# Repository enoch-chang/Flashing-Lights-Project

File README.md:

# Flashing-Lights-Project

Lights will be flashing.

Demo: https://youtu.be/DI44GL3oFzs

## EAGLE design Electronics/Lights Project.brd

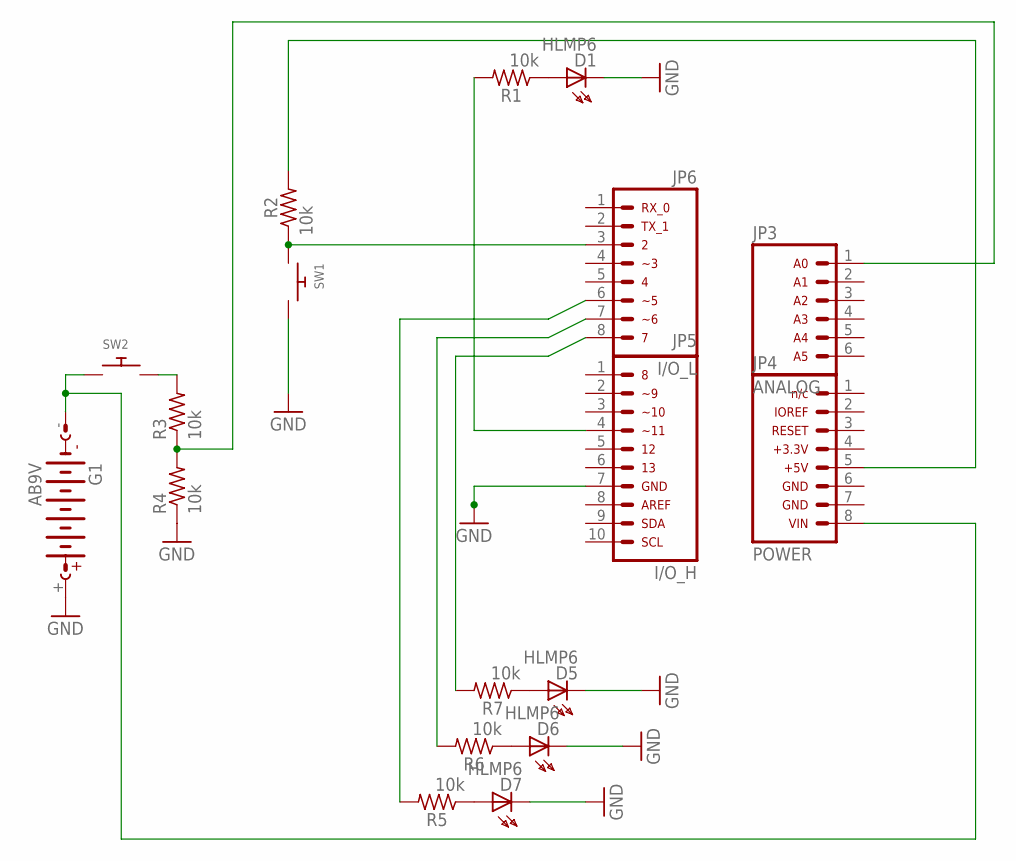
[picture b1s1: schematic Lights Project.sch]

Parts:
D1, D5, D6, D7: HLMP6
G1: AB9V
JP3: ARDUINO_CONN-ANALOGSIP; CONN-1X06
JP4: ARDUINO_CONN-POWERSIP; CONN-1X08
JP5: ARDUINO_CONN-IO_HSIP; CONN-1X10
JP6: ARDUINO_CONN-IO_LSIP; CONN-1X08
R1, R2, R3, R4, R5, R6, R7: 10k; R0805
SW1, SW2: SWITCH_PUSHBUTTONSOFTTOUCHSMD_SJ; PUSHBUTTON_SMD_SJ

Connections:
GND: D1.K, D5.K, D6.K, D7.K, G1.+, JP5.7, R4.1, SW1.P$2
unnamed: G1.-, JP4.8, SW2.P$1
unnamed: JP5.4, R1.2
unnamed: D1.A, R1.1
unnamed: D5.A, R7.1
unnamed: JP6.3, R2.1, SW1.P$1
unnamed: R3.2, SW2.P$2
unnamed: D6.A, R6.1
unnamed: JP6.6, R5.2
unnamed: D7.A, R5.1
unnamed: JP6.7, R6.2
unnamed: JP6.8, R7.2
unnamed: JP3.1, R3.1, R4.2
unnamed: JP4.5, R2.2

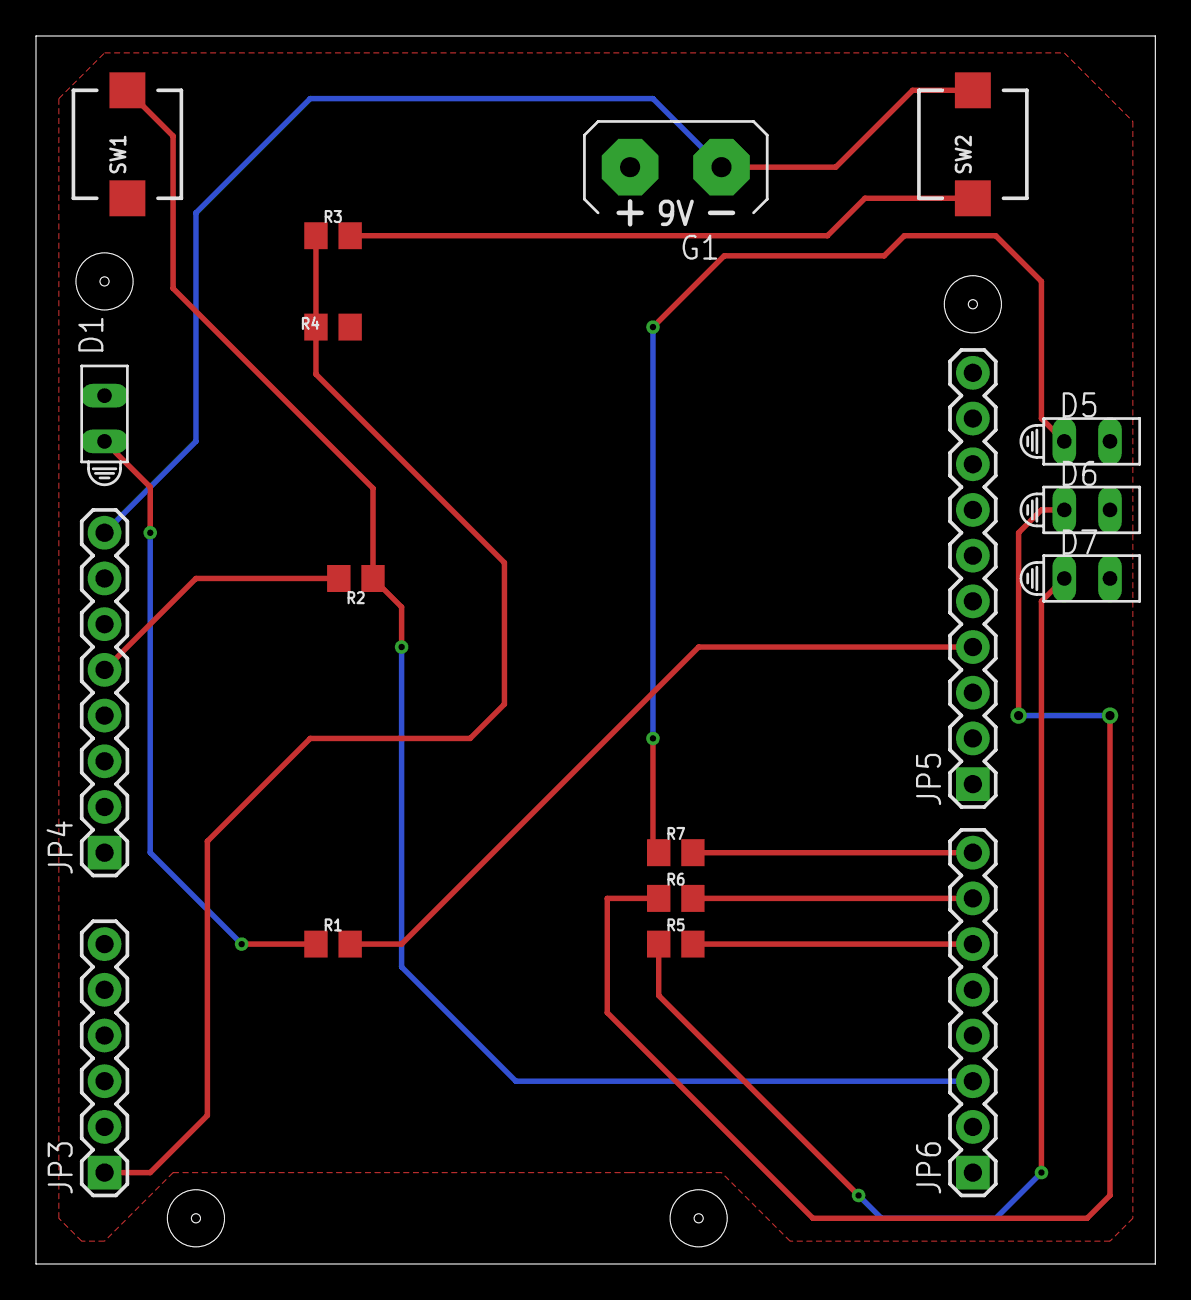
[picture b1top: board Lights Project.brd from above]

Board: 2 copper layers, 62.2 x 68.2 mm, 18 parts (0 on the bottom side), 14 nets.

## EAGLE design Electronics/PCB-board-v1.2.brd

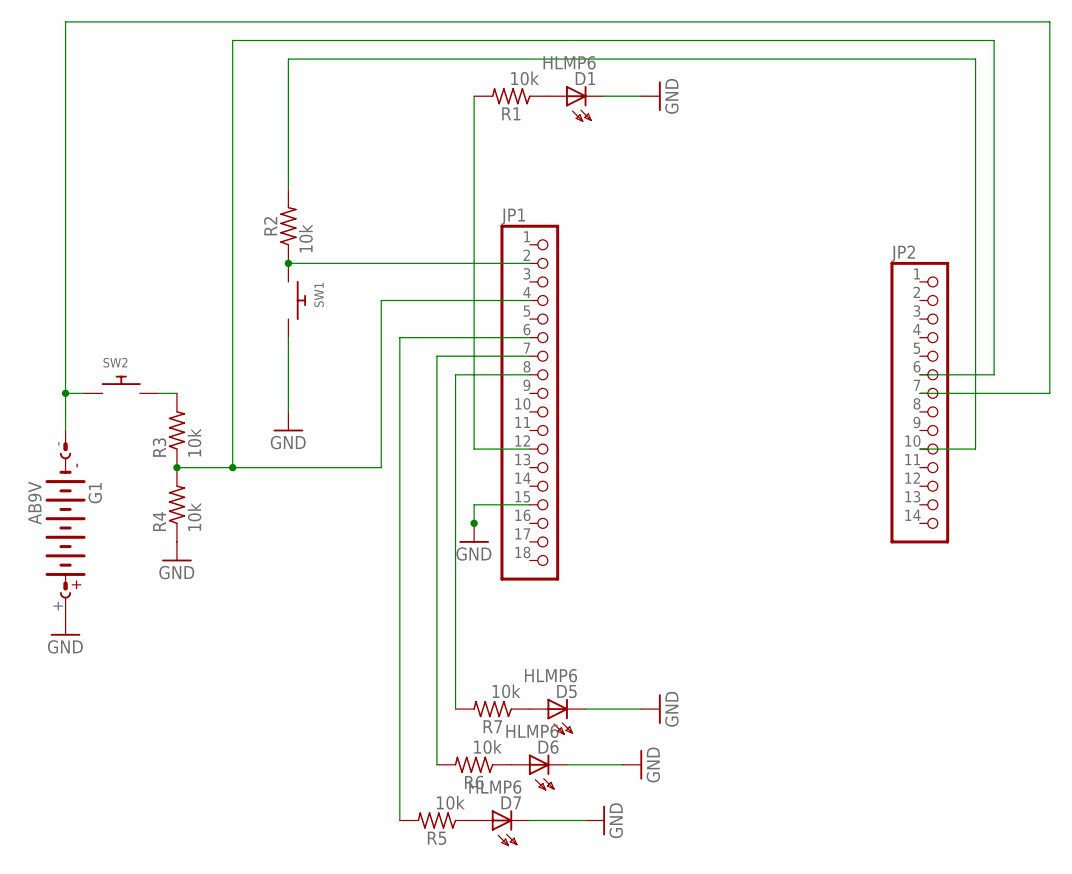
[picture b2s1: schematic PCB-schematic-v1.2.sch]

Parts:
D1, D5, D6, D7: HLMP6
G1: AB9V
JP1: PINHD-1X18; 1X18
JP2: PINHD-1X14; 1X14
R1, R2, R3, R4, R5, R6, R7: 10k; R0805
SW1, SW2: SWITCH_PUSHBUTTONSOFTTOUCHSMD_SJ; PUSHBUTTON_SMD_SJ

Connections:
GND: D1.K, D5.K, D6.K, D7.K, G1.+, JP1.15, R4.1, SW1.P$2
unnamed: G1.-, JP2.7, SW2.P$1
unnamed: JP1.12, R1.2
unnamed: D1.A, R1.1
unnamed: D5.A, R7.1
unnamed: JP1.2, R2.1, SW1.P$1
unnamed: R3.2, SW2.P$2
unnamed: D6.A, R6.1
unnamed: JP1.6, R5.2
unnamed: D7.A, R5.1
unnamed: JP1.7, R6.2
unnamed: JP1.8, R7.2
unnamed: JP1.4, JP2.6, R3.1, R4.2
unnamed: JP2.10, R2.2

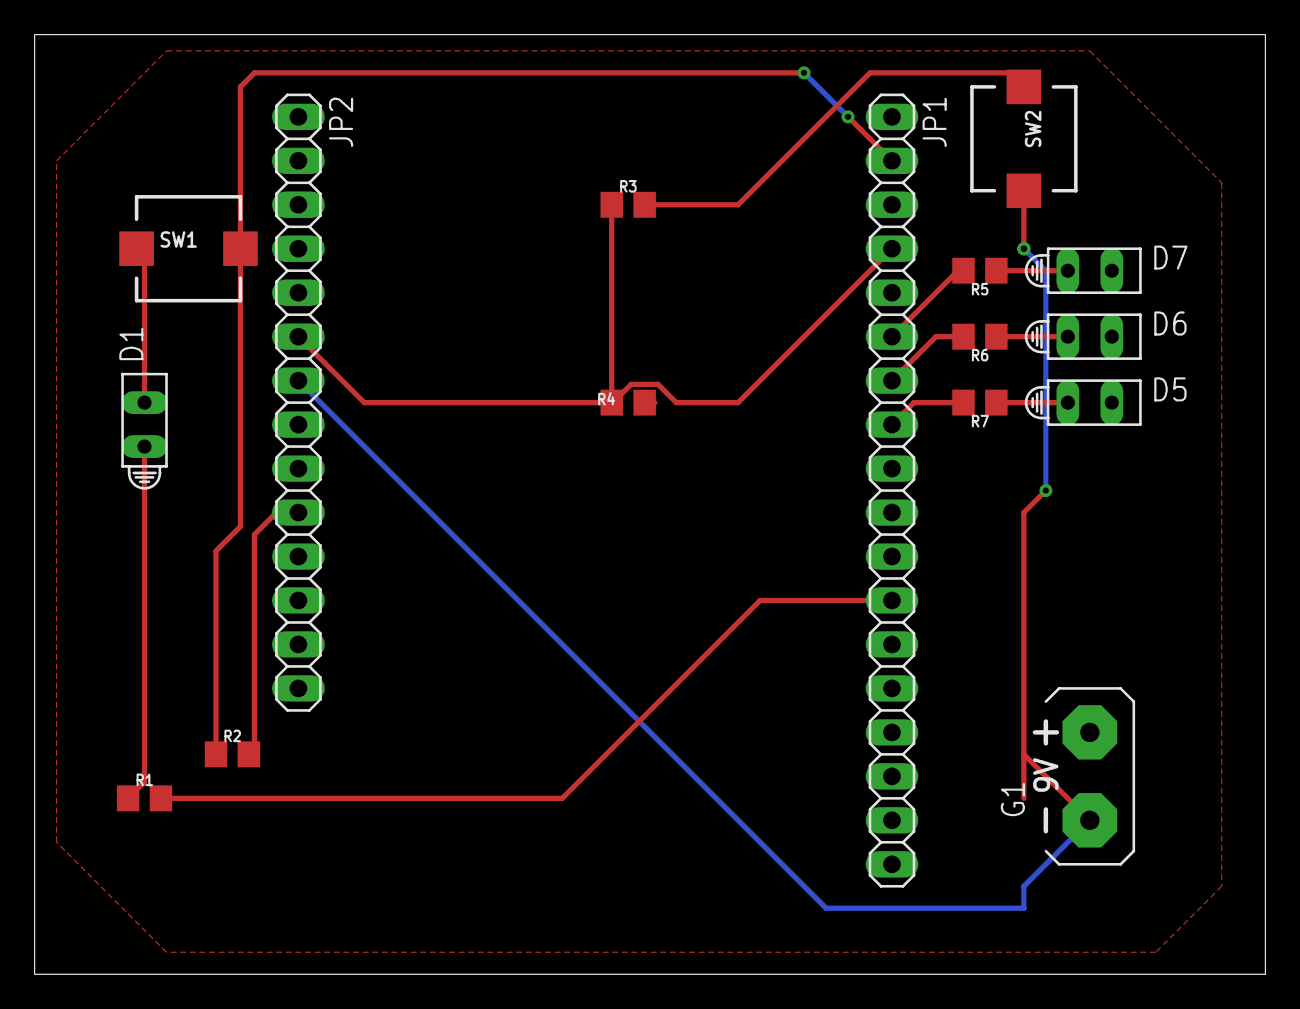
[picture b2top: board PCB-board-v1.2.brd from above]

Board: 2 copper layers, 71.1 x 54.3 mm, 16 parts (0 on the bottom side), 14 nets.

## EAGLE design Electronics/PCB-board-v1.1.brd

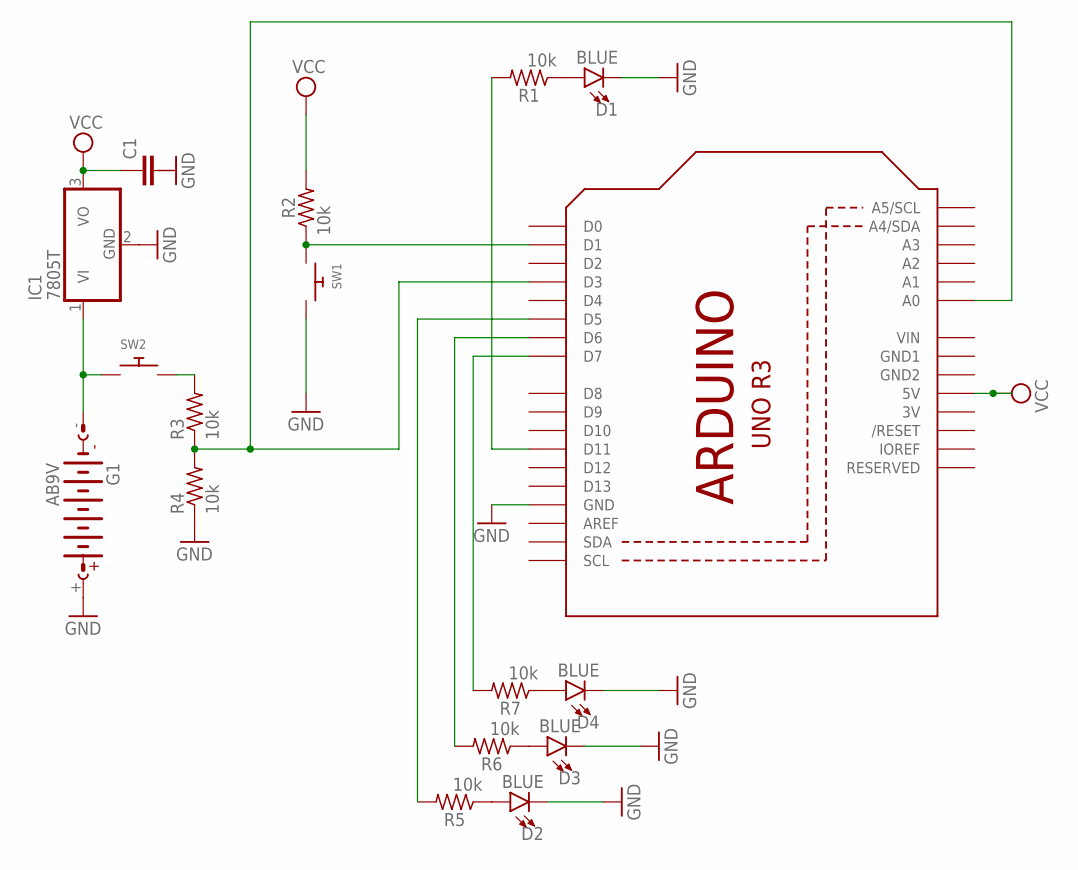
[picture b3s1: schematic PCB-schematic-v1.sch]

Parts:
C1: C10/5; C10B5
D1, D2, D3, D4: BLUE; LED-1206
G1: AB9V
IC1: 7805T; TO220H
R1, R2, R3, R4, R5, R6, R7: 10k; R0805
SW1, SW2: SWITCH_PUSHBUTTONSOFTTOUCHSMD_SJ; PUSHBUTTON_SMD_SJ
U1: ARDUINOR3-BPLACE

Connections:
3V: U1.3V
GND: D1.C, D2.C, D3.C, D4.C, G1.+, IC1.2 (GND), R4.1, SW1.P$2, U1.GND
GND1: U1.GND1
GND2: U1.GND2
unnamed: G1.-, IC1.1 (VI), SW2.P$1
unnamed: R1.2, U1.D11
unnamed: D1.A, R1.1
unnamed: R2.1, SW1.P$1, U1.D1
unnamed: R3.2, SW2.P$2
unnamed: D2.A, R5.1
unnamed: R5.2, U1.D5
unnamed: D3.A, R6.1
unnamed: R6.2, U1.D6
unnamed: R7.2, U1.D7
unnamed: D4.A, R7.1
unnamed: R3.1, R4.2, U1.A0, U1.D3
VCC: C1.1, IC1.3 (VO), R2.2, U1.5V
VIN: U1.VIN

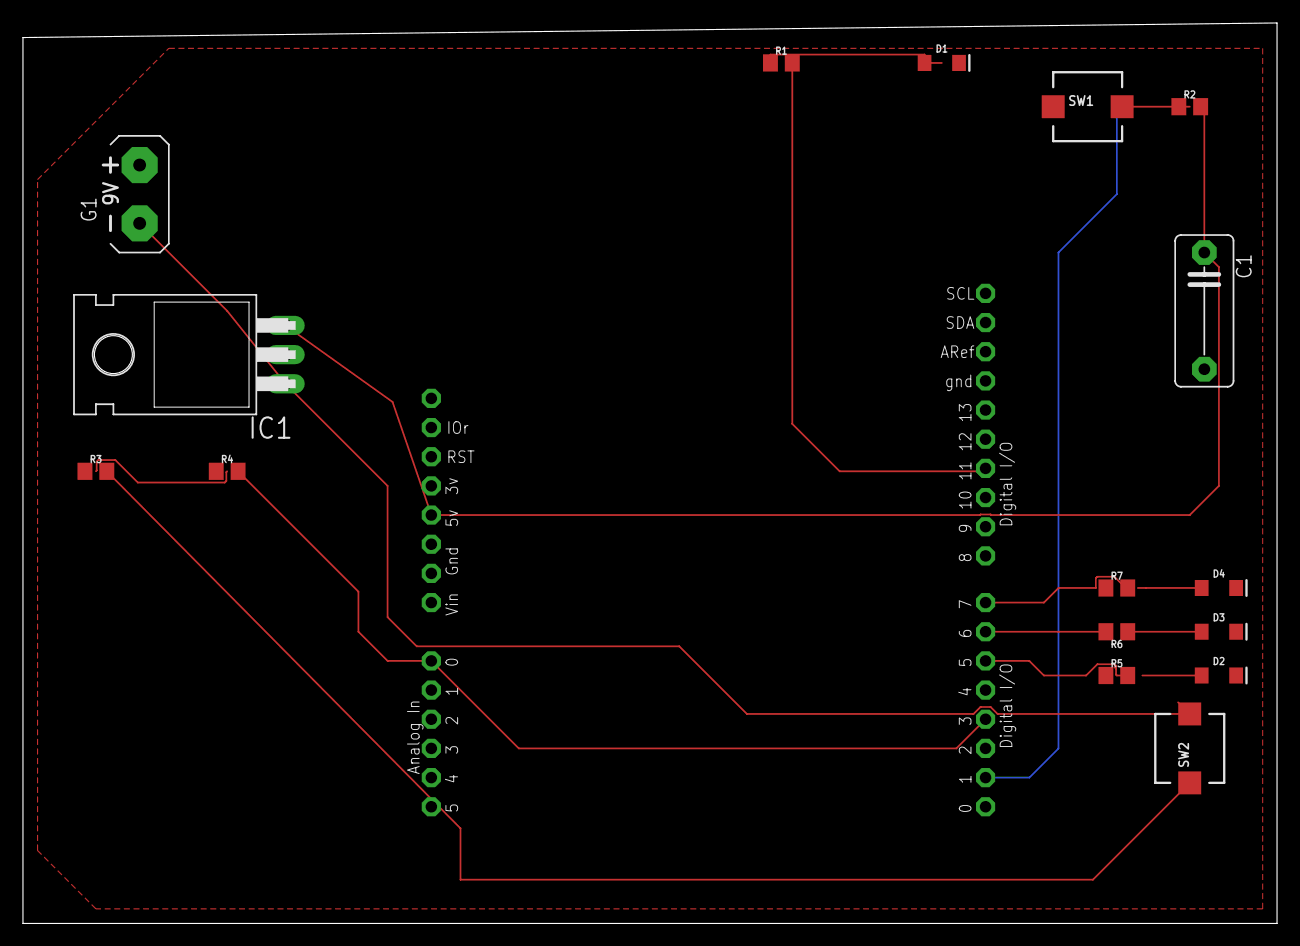
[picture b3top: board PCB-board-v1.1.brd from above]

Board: 2 copper layers, 109.2 x 78.4 mm, 17 parts (0 on the bottom side), 14 nets.

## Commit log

2018-09-30 Created directory
2018-11-01 Add software and circuit sketches
2018-11-01 Modified Circuit Diagram - added LED for battery life indication
2018-11-06 Add Arduino code - main functionality working
2018-11-08 Added ECAD files for review
2018-11-08 Added battery indication functionality
2018-11-08 Added *.sch and *brd files for PCB design
2018-11-12 Rewired and rearranged some components to save space
2018-11-14 Added v1.2 of PCB afte Brinnae's comments
2018-11-19 Added CAD models and drawings
2018-11-21 Completed light case CAD model
2018-11-21 Updated PCB and Schematic: added headers and holes
2018-11-30 Finalized CAD and ECAD designs added
2018-12-02 Added PDFs of finalized PCB design
2018-12-03 Updated CAD drawing
2018-12-14 Updated all electronics files
2018-12-14 Updated CAD model; added *.stl files used for 3D printing
2018-12-14 Added code used for testing and debugging
2018-12-14 Updated code with fixed formatting
2018-12-14 Updated software flowchart
2018-12-14 Added photos

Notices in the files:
parts and their libraries:
SparkFun-LED: Licensing: Creative Commons ShareAlike 4.0 International - https://creativecommons.org/licenses/by-sa/4.0
